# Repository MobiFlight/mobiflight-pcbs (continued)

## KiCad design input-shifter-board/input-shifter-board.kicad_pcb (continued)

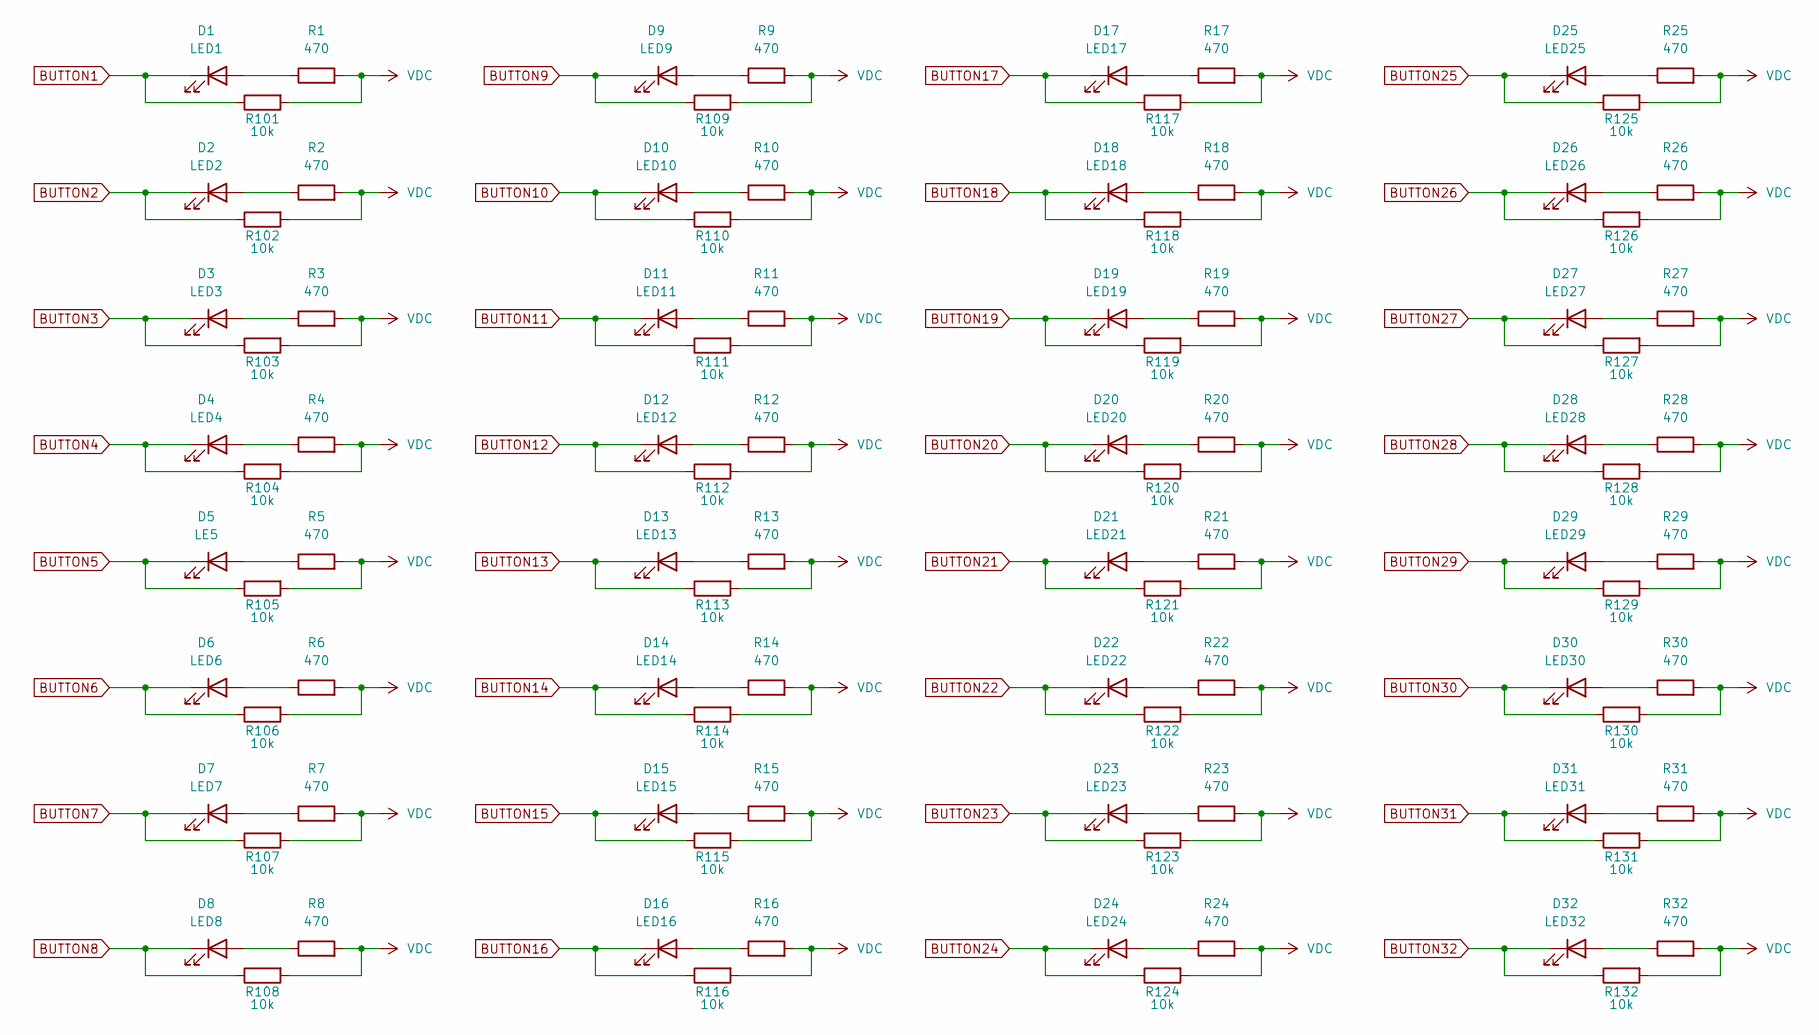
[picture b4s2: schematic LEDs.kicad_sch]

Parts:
D1: LED1; LED_0402_1005Metric; LCSC C130722
D2: LED2; LED_0402_1005Metric; LCSC C130722
D3: LED3; LED_0402_1005Metric; LCSC C130722
D4: LED4; LED_0402_1005Metric; LCSC C130722
D5: LE5; LED_0402_1005Metric; LCSC C130722
D6: LED6; LED_0402_1005Metric; LCSC C130722
D7: LED7; LED_0402_1005Metric; LCSC C130722
D8: LED8; LED_0402_1005Metric; LCSC C130722
D9: LED9; LED_0402_1005Metric; LCSC C130722
D10: LED10; LED_0402_1005Metric; LCSC C130722
D11: LED11; LED_0402_1005Metric; LCSC C130722
D12: LED12; LED_0402_1005Metric; LCSC C130722
D13: LED13; LED_0402_1005Metric; LCSC C130722
D14: LED14; LED_0402_1005Metric; LCSC C130722
D15: LED15; LED_0402_1005Metric; LCSC C130722
D16: LED16; LED_0402_1005Metric; LCSC C130722
D17: LED17; LED_0402_1005Metric; LCSC C130722
D18: LED18; LED_0402_1005Metric; LCSC C130722
D19: LED19; LED_0402_1005Metric; LCSC C130722
D20: LED20; LED_0402_1005Metric; LCSC C130722
D21: LED21; LED_0402_1005Metric; LCSC C130722
D22: LED22; LED_0402_1005Metric; LCSC C130722
D23: LED23; LED_0402_1005Metric; LCSC C130722
D24: LED24; LED_0402_1005Metric; LCSC C130722
D25: LED25; LED_0402_1005Metric; LCSC C130722
D26: LED26; LED_0402_1005Metric; LCSC C130722
D27: LED27; LED_0402_1005Metric; LCSC C130722
D28: LED28; LED_0402_1005Metric; LCSC C130722
D29: LED29; LED_0402_1005Metric; LCSC C130722
D30: LED30; LED_0402_1005Metric; LCSC C130722
D31: LED31; LED_0402_1005Metric; LCSC C130722
D32: LED32; LED_0402_1005Metric; LCSC C130722
R1, R2, R3, R4, R5, R6, R7, R8, R9, R10, R11, R12, R13, R14, R15, R16, R17, R18, R19, R20, R21, R22, R23, R24, R25, R26, R27, R28, R29, R30, R31, R32: 470; R_0402_1005Metric; LCSC C25117
R101, R102, R103, R104, R105, R106, R107, R108, R109, R110, R111, R112, R113, R114, R115, R116, R117, R118, R119, R120, R121, R122, R123, R124, R125, R126, R127, R128, R129, R130, R131, R132: 10k; R_0402_1005Metric; LCSC C25744

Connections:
BUTTON1: D1.1 (K), R101.1; also elsewhere on the board
BUTTON2: D2.1 (K), R102.1; also elsewhere on the board
BUTTON3: D3.1 (K), R103.1; also elsewhere on the board
BUTTON4: D4.1 (K), R104.1; also elsewhere on the board
BUTTON5: D5.1 (K), R105.1; also elsewhere on the board
BUTTON6: D6.1 (K), R106.1; also elsewhere on the board
BUTTON7: D7.1 (K), R107.1; also elsewhere on the board
BUTTON8: D8.1 (K), R108.1; also elsewhere on the board
BUTTON9: D9.1 (K), R109.1; also elsewhere on the board
BUTTON10: D10.1 (K), R110.1; also elsewhere on the board
BUTTON11: D11.1 (K), R111.1; also elsewhere on the board
BUTTON12: D12.1 (K), R112.1; also elsewhere on the board
BUTTON13: D13.1 (K), R113.1; also elsewhere on the board
BUTTON14: D14.1 (K), R114.1; also elsewhere on the board
BUTTON15: D15.1 (K), R115.1; also elsewhere on the board
BUTTON16: D16.1 (K), R116.1; also elsewhere on the board
BUTTON17: D17.1 (K), R117.1; also elsewhere on the board
BUTTON18: D18.1 (K), R118.1; also elsewhere on the board
BUTTON19: D19.1 (K), R119.1; also elsewhere on the board
BUTTON20: D20.1 (K), R120.1; also elsewhere on the board
BUTTON21: D21.1 (K), R121.1; also elsewhere on the board
BUTTON22: D22.1 (K), R122.1; also elsewhere on the board
BUTTON23: D23.1 (K), R123.1; also elsewhere on the board
BUTTON24: D24.1 (K), R124.1; also elsewhere on the board
BUTTON25: D25.1 (K), R125.1; also elsewhere on the board
BUTTON26: D26.1 (K), R126.1; also elsewhere on the board
BUTTON27: D27.1 (K), R127.1; also elsewhere on the board
BUTTON28: D28.1 (K), R128.1; also elsewhere on the board
BUTTON29: D29.1 (K), R129.1; also elsewhere on the board
BUTTON30: D30.1 (K), R130.1; also elsewhere on the board
BUTTON31: D31.1 (K), R131.1; also elsewhere on the board
BUTTON32: D32.1 (K), R132.1; also elsewhere on the board
unnamed: D1.2 (A), R1.1
unnamed: D2.2 (A), R2.1
unnamed: D3.2 (A), R3.1
unnamed: D4.2 (A), R4.1
unnamed: D5.2 (A), R5.1
unnamed: D6.2 (A), R6.1
unnamed: D7.2 (A), R7.1
unnamed: D8.2 (A), R8.1
unnamed: D9.2 (A), R9.1
unnamed: D10.2 (A), R10.1
unnamed: D11.2 (A), R11.1
unnamed: D12.2 (A), R12.1
unnamed: D13.2 (A), R13.1
unnamed: D14.2 (A), R14.1
unnamed: D15.2 (A), R15.1
unnamed: D16.2 (A), R16.1
unnamed: D17.2 (A), R17.1
unnamed: D18.2 (A), R18.1
unnamed: D19.2 (A), R19.1
unnamed: D20.2 (A), R20.1
unnamed: D21.2 (A), R21.1
unnamed: D22.2 (A), R22.1
unnamed: D23.2 (A), R23.1
unnamed: D24.2 (A), R24.1
unnamed: D25.2 (A), R25.1
unnamed: D26.2 (A), R26.1
unnamed: D27.2 (A), R27.1
unnamed: D28.2 (A), R28.1
unnamed: D29.2 (A), R29.1
unnamed: D30.2 (A), R30.1
unnamed: D31.2 (A), R31.1
unnamed: D32.2 (A), R32.1
VDC: R1.2, R2.2, R3.2, R4.2, R5.2, R6.2, R7.2, R8.2, R9.2, R10.2, R11.2, R12.2, R13.2, R14.2, R15.2, R16.2, R17.2, R18.2, R19.2, R20.2, R21.2, R22.2, R23.2, R24.2, R25.2, R26.2, R27.2, R28.2, R29.2, R30.2, R31.2, R32.2, R101.2, R102.2, R103.2, R104.2, R105.2, R106.2, R107.2, R108.2, R109.2, R110.2, R111.2, R112.2, R113.2, R114.2, R115.2, R116.2, R117.2, R118.2, R119.2, R120.2, R121.2, R122.2, R123.2, R124.2, R125.2, R126.2, R127.2, R128.2, R129.2, R130.2, R131.2, R132.2; also elsewhere on the board

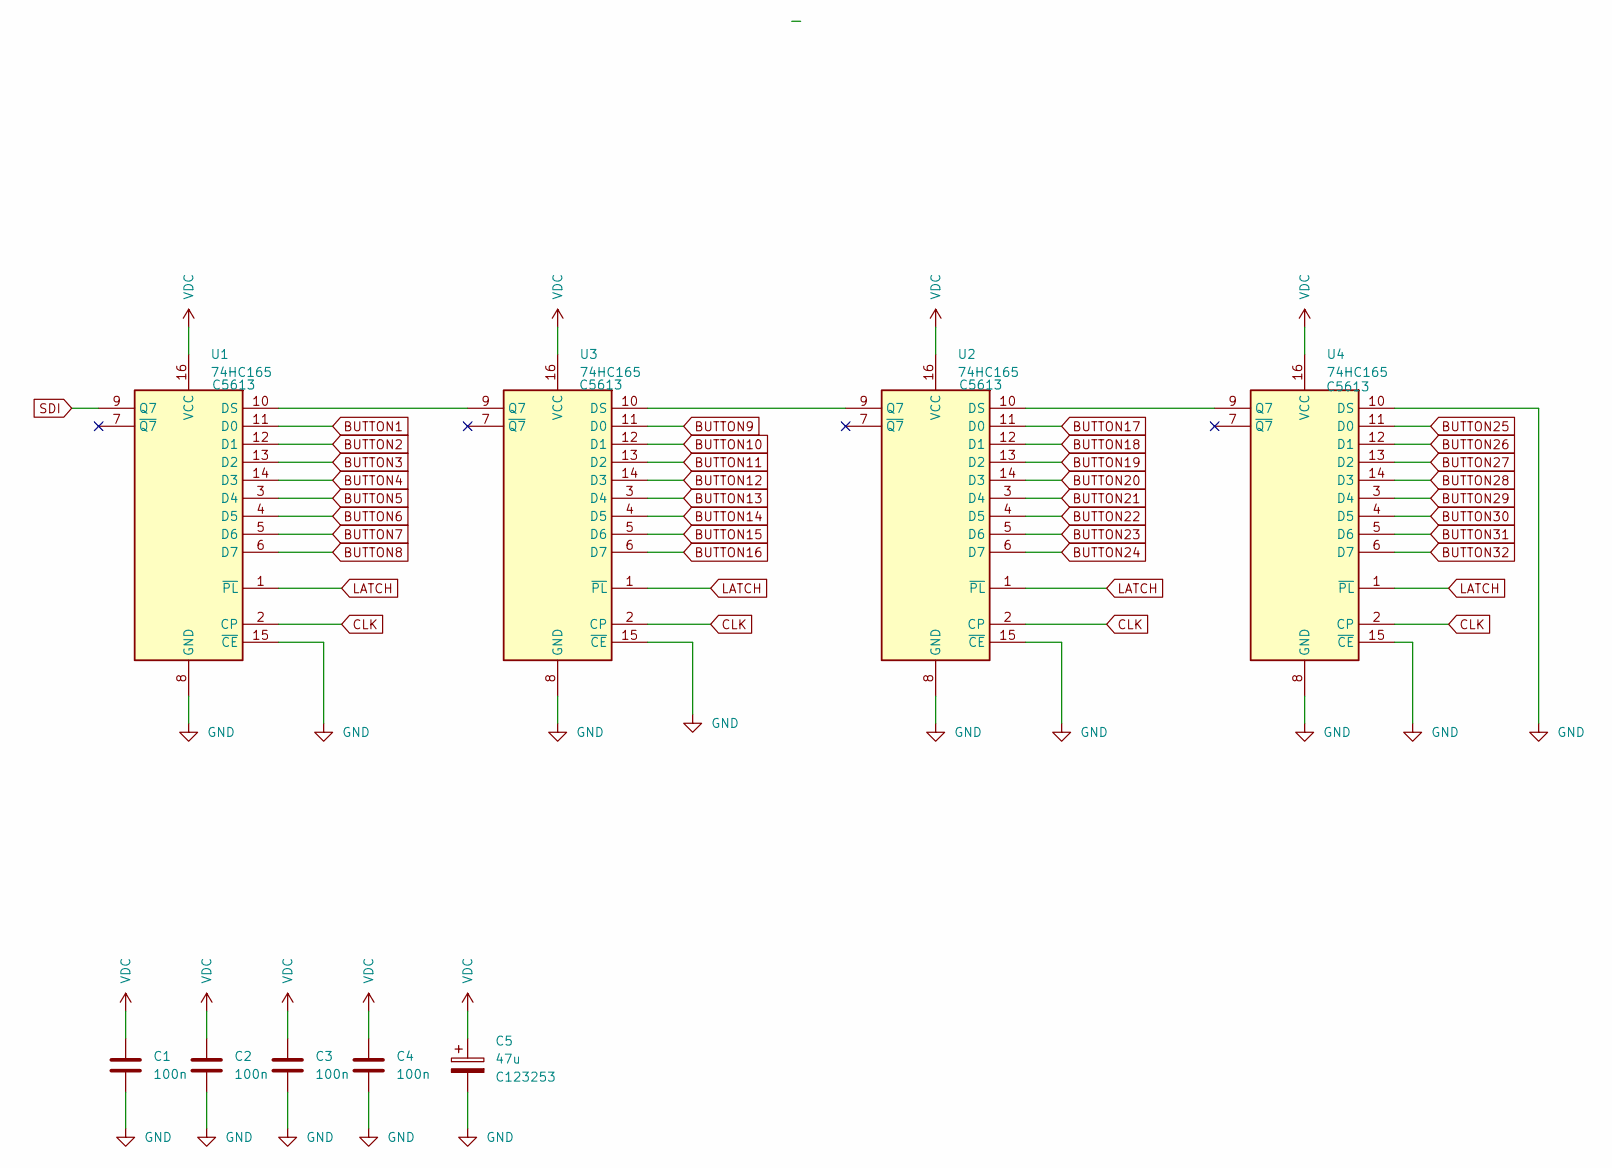
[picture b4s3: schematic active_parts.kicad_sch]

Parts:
C1, C2, C3, C4: 100n; C_0805_2012Metric; LCSC C49678
C5: 47u; CP_EIA-3528-21_Kemet-B; LCSC C123253
U1, U2, U3, U4: 74HC165; SOIC-16_3.9x9.9mm_P1.27mm; LCSC C5613

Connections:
BUTTON1: U1.11 (D0); also elsewhere on the board
BUTTON2: U1.12 (D1); also elsewhere on the board
BUTTON3: U1.13 (D2); also elsewhere on the board
BUTTON4: U1.14 (D3); also elsewhere on the board
BUTTON5: U1.3 (D4); also elsewhere on the board
BUTTON6: U1.4 (D5); also elsewhere on the board
BUTTON7: U1.5 (D6); also elsewhere on the board
BUTTON8: U1.6 (D7); also elsewhere on the board
BUTTON9: U3.11 (D0); also elsewhere on the board
BUTTON10: U3.12 (D1); also elsewhere on the board
BUTTON11: U3.13 (D2); also elsewhere on the board
BUTTON12: U3.14 (D3); also elsewhere on the board
BUTTON13: U3.3 (D4); also elsewhere on the board
BUTTON14: U3.4 (D5); also elsewhere on the board
BUTTON15: U3.5 (D6); also elsewhere on the board
BUTTON16: U3.6 (D7); also elsewhere on the board
BUTTON17: U2.11 (D0); also elsewhere on the board
BUTTON18: U2.12 (D1); also elsewhere on the board
BUTTON19: U2.13 (D2); also elsewhere on the board
BUTTON20: U2.14 (D3); also elsewhere on the board
BUTTON21: U2.3 (D4); also elsewhere on the board
BUTTON22: U2.4 (D5); also elsewhere on the board
BUTTON23: U2.5 (D6); also elsewhere on the board
BUTTON24: U2.6 (D7); also elsewhere on the board
BUTTON25: U4.11 (D0); also elsewhere on the board
BUTTON26: U4.12 (D1); also elsewhere on the board
BUTTON27: U4.13 (D2); also elsewhere on the board
BUTTON28: U4.14 (D3); also elsewhere on the board
BUTTON29: U4.3 (D4); also elsewhere on the board
BUTTON30: U4.4 (D5); also elsewhere on the board
BUTTON31: U4.5 (D6); also elsewhere on the board
BUTTON32: U4.6 (D7); also elsewhere on the board
CLK: U1.2 (CP), U2.2 (CP), U3.2 (CP), U4.2 (CP); also elsewhere on the board
GND: C1.2, C2.2, C3.2, C4.2, C5.2, U1.8 (GND), U1.15 (~CE), U2.8 (GND), U2.15 (~CE), U3.8 (GND), U3.15 (~CE), U4.8 (GND), U4.10 (DS), U4.15 (~CE); also elsewhere on the board
LATCH: U1.1 (~PL), U2.1 (~PL), U3.1 (~PL), U4.1 (~PL); also elsewhere on the board
unnamed: U1.10 (DS), U3.9 (Q7)
unnamed: U2.10 (DS), U4.9 (Q7)
unnamed: U2.9 (Q7), U3.10 (DS)
SDI: U1.9 (Q7); also elsewhere on the board
VDC: C1.1, C2.1, C3.1, C4.1, C5.1, U1.16 (VCC), U2.16 (VCC), U3.16 (VCC), U4.16 (VCC); also elsewhere on the board

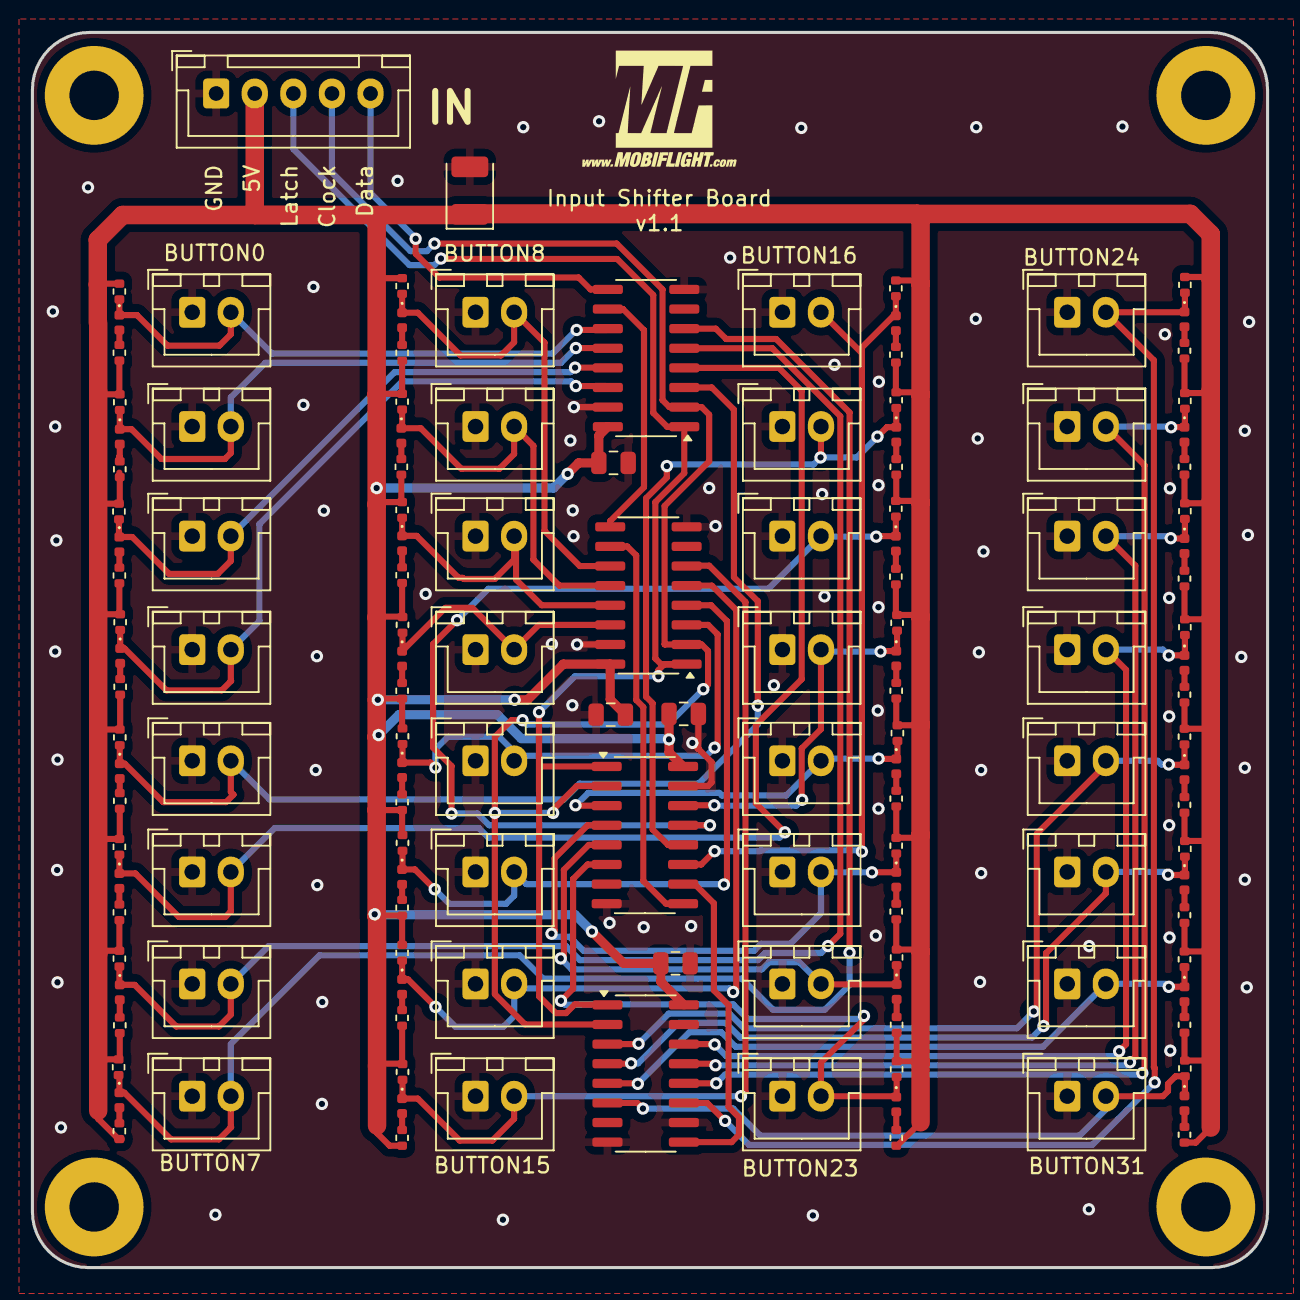
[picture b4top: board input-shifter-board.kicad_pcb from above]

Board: 2 copper layers, 80.0 x 80.0 mm, 144 parts (1 on the bottom side), 72 nets.

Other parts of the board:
G2, G2#2: LOGO; MobiFlight-Logo-Small

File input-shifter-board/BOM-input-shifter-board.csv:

Comment,Designator,Footprint,LCSC,Quantity
47u,C5,CP_EIA-3528-21_Kemet-B,C123253,1
LED1,"D1,D10,D11,D12,D13,D14,D15,D16,D17,D18,D19,D2,D20,D21,D22,D23,D24,D25,D26,D27,D28,D29,D3,D30,D31,D32,D4,D5,D6,D7,D8,D9",LED_0402_1005Metric,C130722,32
BUTTON1,"J1,J10,J11,J12,J13,J14,J15,J16,J17,J18,J19,J2,J20,J21,J22,J23,J24,J25,J26,J27,J28,J29,J3,J30,J31,J32,J4,J5,J6,J7,J8,J9",JST_XH_B2B-XH-A_1x02_P2.50mm_Vertical,C20079,32
Data,J33,JST_XH_B5B-XH-A_1x05_P2.50mm_Vertical,C2318,1
470,"R1,R10,R11,R12,R13,R14,R15,R16,R17,R18,R19,R2,R20,R21,R22,R23,R24,R25,R26,R27,R28,R29,R3,R30,R31,R32,R4,R5,R6,R7,R8,R9",R_0402_1005Metric,C25117,32
10k,"R101,R102,R103,R104,R105,R106,R107,R108,R109,R110,R111,R112,R113,R114,R115,R116,R117,R118,R119,R120,R121,R122,R123,R124,R125,R126,R127,R128,R129,R130,R131,R132",R_0402_1005Metric,C25744,32
100n,"C1,C2,C3,C4",C_0805_2012Metric,C49678,4
74HC165,"U1,U2,U3,U4",SOIC-16_3.9x9.9mm_P1.27mm,C5613,4

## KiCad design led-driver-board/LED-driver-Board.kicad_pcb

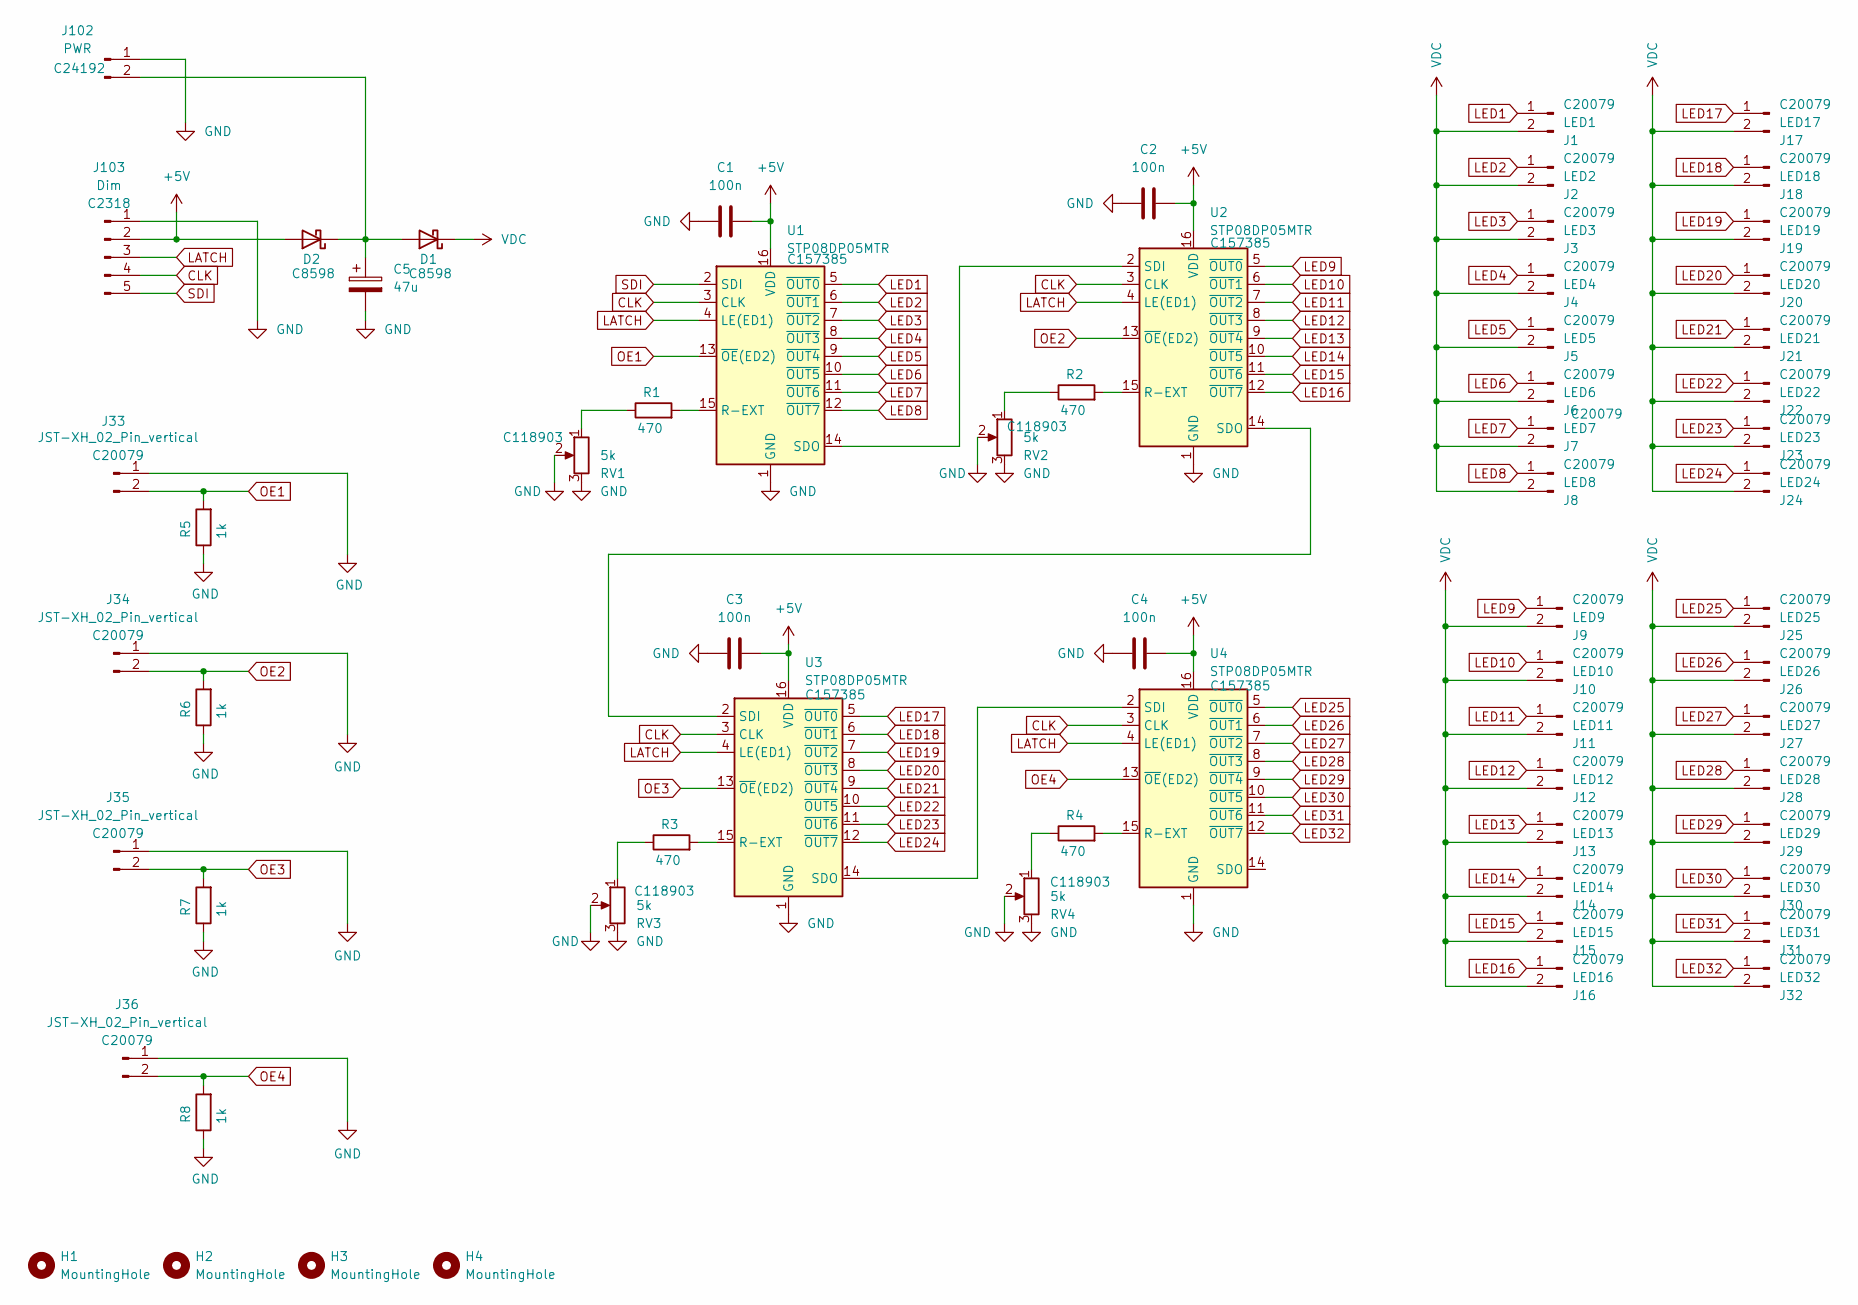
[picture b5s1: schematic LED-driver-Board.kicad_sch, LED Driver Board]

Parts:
C1, C2, C3, C4: 100n; C_0805_2012Metric; LCSC C28233
C5: 47u; CP_EIA-3528-21_Kemet-B; LCSC C123253
D1, D2: D_Schottky_B5819W-SL; D_SOD-123; LCSC C8598
H1, H2, H3, H4: MountingHole; MountingHole_3.2mm_M3_Pad
J1: LED1; JST_XH_B2B-XH-A_1x02_P2.50mm_Vertical; LCSC C20079
J2: LED2; JST_XH_B2B-XH-A_1x02_P2.50mm_Vertical; LCSC C20079
J3: LED3; JST_XH_B2B-XH-A_1x02_P2.50mm_Vertical; LCSC C20079
J4: LED4; JST_XH_B2B-XH-A_1x02_P2.50mm_Vertical; LCSC C20079
J5: LED5; JST_XH_B2B-XH-A_1x02_P2.50mm_Vertical; LCSC C20079
J6: LED6; JST_XH_B2B-XH-A_1x02_P2.50mm_Vertical; LCSC C20079
J7: LED7; JST_XH_B2B-XH-A_1x02_P2.50mm_Vertical; LCSC C20079
J8: LED8; JST_XH_B2B-XH-A_1x02_P2.50mm_Vertical; LCSC C20079
J9: LED9; JST_XH_B2B-XH-A_1x02_P2.50mm_Vertical; LCSC C20079
J10: LED10; JST_XH_B2B-XH-A_1x02_P2.50mm_Vertical; LCSC C20079
J11: LED11; JST_XH_B2B-XH-A_1x02_P2.50mm_Vertical; LCSC C20079
J12: LED12; JST_XH_B2B-XH-A_1x02_P2.50mm_Vertical; LCSC C20079
J13: LED13; JST_XH_B2B-XH-A_1x02_P2.50mm_Vertical; LCSC C20079
J14: LED14; JST_XH_B2B-XH-A_1x02_P2.50mm_Vertical; LCSC C20079
J15: LED15; JST_XH_B2B-XH-A_1x02_P2.50mm_Vertical; LCSC C20079
J16: LED16; JST_XH_B2B-XH-A_1x02_P2.50mm_Vertical; LCSC C20079
J17: LED17; JST_XH_B2B-XH-A_1x02_P2.50mm_Vertical; LCSC C20079
J18: LED18; JST_XH_B2B-XH-A_1x02_P2.50mm_Vertical; LCSC C20079
J19: LED19; JST_XH_B2B-XH-A_1x02_P2.50mm_Vertical; LCSC C20079
J20: LED20; JST_XH_B2B-XH-A_1x02_P2.50mm_Vertical; LCSC C20079
J21: LED21; JST_XH_B2B-XH-A_1x02_P2.50mm_Vertical; LCSC C20079
J22: LED22; JST_XH_B2B-XH-A_1x02_P2.50mm_Vertical; LCSC C20079
J23: LED23; JST_XH_B2B-XH-A_1x02_P2.50mm_Vertical; LCSC C20079
J24: LED24; JST_XH_B2B-XH-A_1x02_P2.50mm_Vertical; LCSC C20079
J25: LED25; JST_XH_B2B-XH-A_1x02_P2.50mm_Vertical; LCSC C20079
J26: LED26; JST_XH_B2B-XH-A_1x02_P2.50mm_Vertical; LCSC C20079
J27: LED27; JST_XH_B2B-XH-A_1x02_P2.50mm_Vertical; LCSC C20079
J28: LED28; JST_XH_B2B-XH-A_1x02_P2.50mm_Vertical; LCSC C20079
J29: LED29; JST_XH_B2B-XH-A_1x02_P2.50mm_Vertical; LCSC C20079
J30: LED30; JST_XH_B2B-XH-A_1x02_P2.50mm_Vertical; LCSC C20079
J31: LED31; JST_XH_B2B-XH-A_1x02_P2.50mm_Vertical; LCSC C20079
J32: LED32; JST_XH_B2B-XH-A_1x02_P2.50mm_Vertical; LCSC C20079
J33, J34, J35, J36: JST-XH_02_Pin_vertical; JST_XH_B2B-XH-A_1x02_P2.50mm_Vertical; LCSC C20079
J102: PWR; JST_XH_B2B-XH-A_1x02_P2.50mm_Vertical; LCSC C24192
J103: Dim; JST_XH_B5B-XH-A_1x05_P2.50mm_Vertical; LCSC C2318
R1, R2, R3, R4: 470; R_0805_2012Metric; LCSC C17710
R5, R6, R7, R8: 1k; R_0805_2012Metric; LCSC C17513
RV1, RV2, RV3, RV4: 5k; Potentiometer_Bochen_3362P_Vertical; LCSC C118903
U1, U2, U3, U4: STP08DP05MTR; SO-16_3.9x9.9mm_P1.27mm; LCSC C157385

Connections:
+5V: C1.2, C2.2, C3.2, C4.2, D2.2 (A), J103.2, U1.16 (VDD), U2.16 (VDD), U3.16 (VDD), U4.16 (VDD)
CLK: J103.4, U1.3 (CLK), U2.3 (CLK), U3.3 (CLK), U4.3 (CLK)
GND: C1.1, C2.1, C3.1, C4.1, C5.2, J33.1, J34.1, J35.1, J36.1, J102.1, J103.1, R5.1, R6.1, R7.1, R8.1, RV1.2, RV1.3, RV2.2, RV2.3, RV3.2, RV3.3, RV4.2, RV4.3, U1.1 (GND), U2.1 (GND), U3.1 (GND), U4.1 (GND)
LATCH: J103.3, U1.4 (LE(ED1)), U2.4 (LE(ED1)), U3.4 (LE(ED1)), U4.4 (LE(ED1))
LED1: J1.1, U1.5 (~OUT0)
LED2: J2.1, U1.6 (~OUT1)
LED3: J3.1, U1.7 (~OUT2)
LED4: J4.1, U1.8 (~OUT3)
LED5: J5.1, U1.9 (~OUT4)
LED6: J6.1, U1.10 (~OUT5)
LED7: J7.1, U1.11 (~OUT6)
LED8: J8.1, U1.12 (~OUT7)
LED9: J9.1, U2.5 (~OUT0)
LED10: J10.1, U2.6 (~OUT1)
LED11: J11.1, U2.7 (~OUT2)
LED12: J12.1, U2.8 (~OUT3)
LED13: J13.1, U2.9 (~OUT4)
LED14: J14.1, U2.10 (~OUT5)
LED15: J15.1, U2.11 (~OUT6)
LED16: J16.1, U2.12 (~OUT7)
LED17: J17.1, U3.5 (~OUT0)
LED18: J18.1, U3.6 (~OUT1)
LED19: J19.1, U3.7 (~OUT2)
LED20: J20.1, U3.8 (~OUT3)
LED21: J21.1, U3.9 (~OUT4)
LED22: J22.1, U3.10 (~OUT5)
LED23: J23.1, U3.11 (~OUT6)
LED24: J24.1, U3.12 (~OUT7)
LED25: J25.1, U4.5 (~OUT0)
LED26: J26.1, U4.6 (~OUT1)
LED27: J27.1, U4.7 (~OUT2)
LED28: J28.1, U4.8 (~OUT3)
LED29: J29.1, U4.9 (~OUT4)
LED30: J30.1, U4.10 (~OUT5)
LED31: J31.1, U4.11 (~OUT6)
LED32: J32.1, U4.12 (~OUT7)
unnamed: C5.1, D1.2 (A), D2.1 (K), J102.2
unnamed: R1.1, RV1.1
unnamed: R2.1, RV2.1
unnamed: R3.1, RV3.1
unnamed: R4.1, RV4.1
unnamed: R1.2, U1.15 (R-EXT)
unnamed: U1.14 (SDO), U2.2 (SDI)
unnamed: R2.2, U2.15 (R-EXT)
unnamed: U2.14 (SDO), U3.2 (SDI)
unnamed: R3.2, U3.15 (R-EXT)
unnamed: U3.14 (SDO), U4.2 (SDI)
unnamed: R4.2, U4.15 (R-EXT)
OE1: J33.2, R5.2, U1.13 (~OE(ED2))
OE2: J34.2, R6.2, U2.13 (~OE(ED2))
OE3: J35.2, R7.2, U3.13 (~OE(ED2))
OE4: J36.2, R8.2, U4.13 (~OE(ED2))
SDI: J103.5, U1.2 (SDI)
VDC: D1.1 (K), J1.2, J2.2, J3.2, J4.2, J5.2, J6.2, J7.2, J8.2, J9.2, J10.2, J11.2, J12.2, J13.2, J14.2, J15.2, J16.2, J17.2, J18.2, J19.2, J20.2, J21.2, J22.2, J23.2, J24.2, J25.2, J26.2, J27.2, J28.2, J29.2, J30.2, J31.2, J32.2

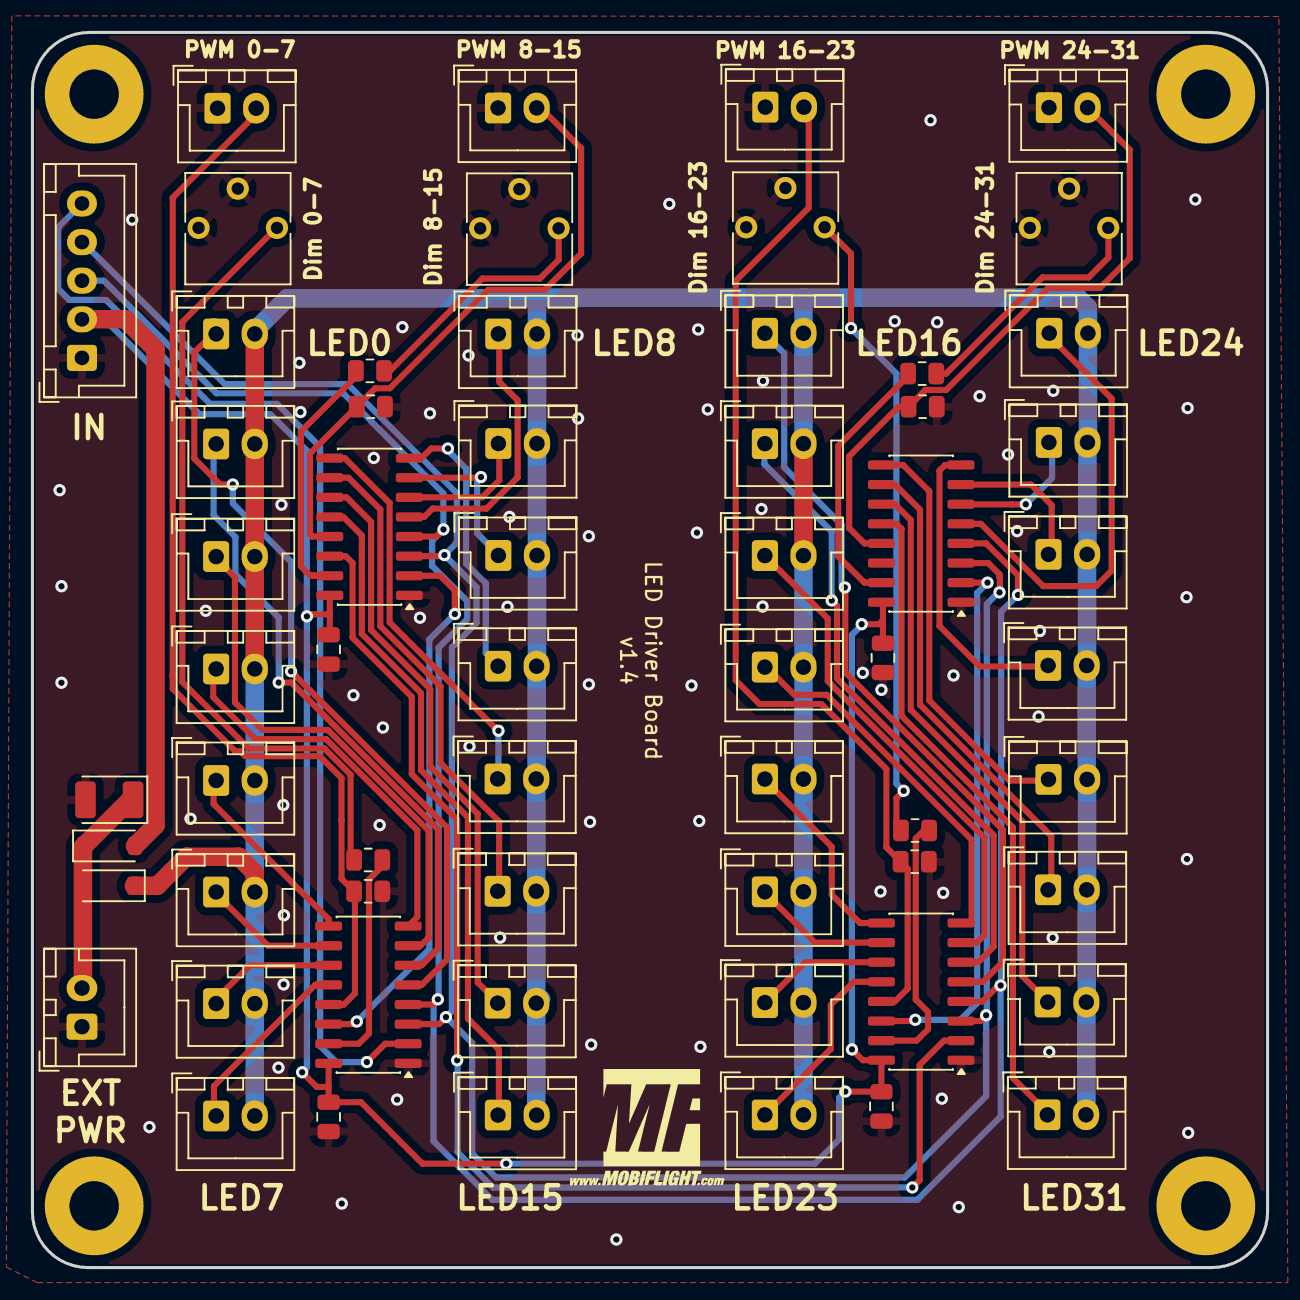
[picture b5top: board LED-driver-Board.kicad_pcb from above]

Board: 2 copper layers, 80.0 x 80.0 mm, 67 parts (1 on the bottom side), 54 nets.

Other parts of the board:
G2, G2#2: LOGO; MobiFlight-Logo-Small

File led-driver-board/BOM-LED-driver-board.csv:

Comment,Designator,Footprint,LCSC,Quantity
47u,C5,CP_EIA-3528-21_Kemet-B,C123253,1
STP08DP05MTR,"U1,U2,U3,U4",SO-16_3.9x9.9mm_P1.27mm,C157385,4
100,"R1,R2,R3,R4",R_0805_2012Metric,C17408,4
1k,"R5,R6,R7,R8",R_0805_2012Metric,C17513,4
LED1,"J1,J10,J102,J11,J12,J13,J14,J15,J16,J17,J18,J19,J2,J20,J21,J22,J23,J24,J25,J26,J27,J28,J29,J3,J30,J31,J32,J33,J34,J35,J36,J4,J5,J6,J7,J8,J9",JST_XH_B2B-XH-A_1x02_P2.50mm_Vertical,C20079,37
Dim,J103,JST_XH_B5B-XH-A_1x05_P2.50mm_Vertical,C2318,1
100n,"C1,C2,C3,C4",C_0805_2012Metric,C28233,4
5k,"RV1,RV2,RV3,RV4",Potentiometer_Bourns_3214J_Horizontal,C58391,4

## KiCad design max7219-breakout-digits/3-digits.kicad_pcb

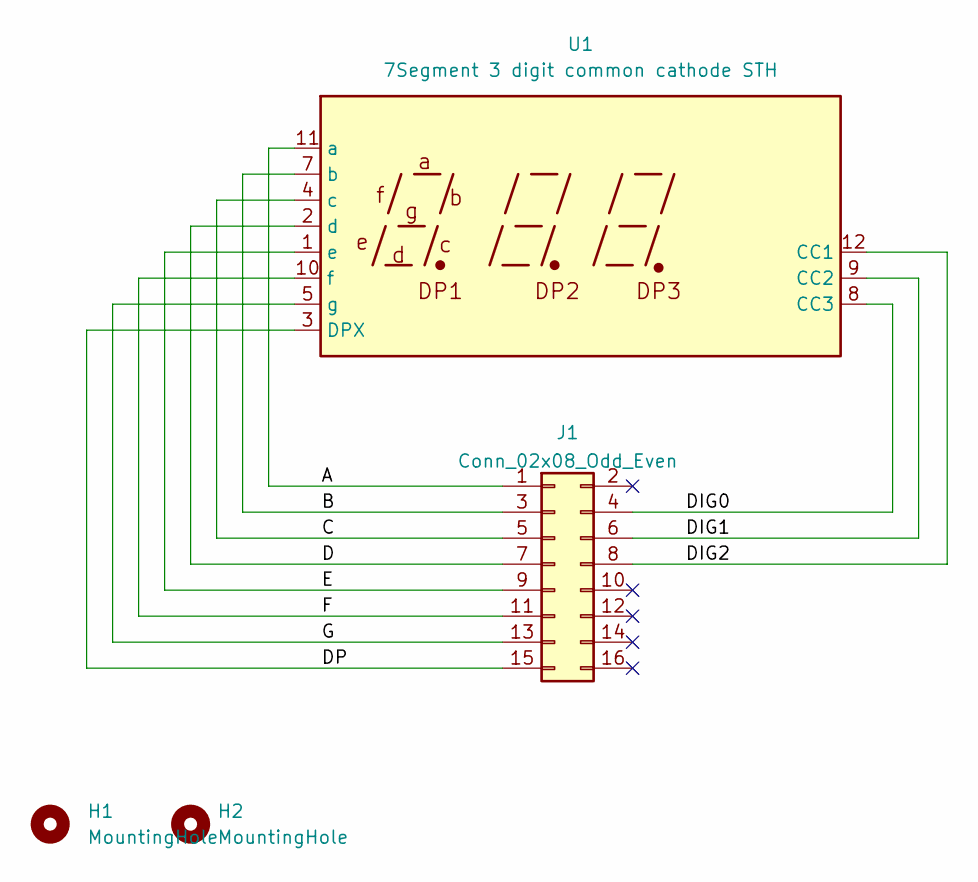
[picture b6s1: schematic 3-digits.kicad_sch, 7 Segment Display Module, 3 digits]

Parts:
H1, H2: MountingHole; MountingHole_3.2mm_M3_Pad
J1: Conn_02x08_Odd_Even; IDC-Header_2x08_P2.54mm_Vertical
U1: 7Segment 3 digit common cathode STH; STH_7_3 Digits_0.28_CC

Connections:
/A: J1.1, U1.11 (a)
/B: J1.3, U1.7 (b)
/C: J1.5, U1.4 (c)
/D: J1.7, U1.2 (d)
/DIG0: J1.4, U1.8 (CC3)
/DIG1: J1.6, U1.9 (CC2)
/DIG2: J1.8, U1.12 (CC1)
/DP: J1.15, U1.3 (DPX)
/E: J1.9, U1.1 (e)
/F: J1.11, U1.10 (f)
/G: J1.13, U1.5 (g)

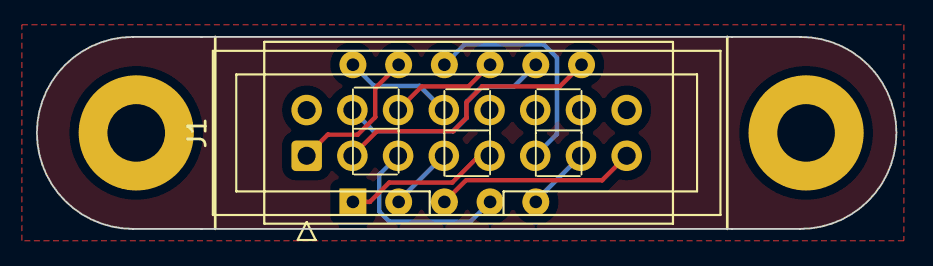
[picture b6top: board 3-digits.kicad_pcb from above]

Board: 2 copper layers, 47.8 x 10.7 mm, 5 parts (1 on the bottom side), 11 nets.

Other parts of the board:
G2: LOGO; MobiFlight-Logo-Small
